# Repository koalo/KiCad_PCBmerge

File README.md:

# KiCad_PCBmerge

A Python module for merging multiple KiCad PCBs

By using this module you can merge multiple KiCad PCBs by aligning them at a common part.
For example for merging a addon board to a base board and align them at a pin header use the following steps.

1. Create a KiCad PCB for the base PCB and add a pin header where the addon board shall be connected.
2. Change the value of the pin header to a specific value, for example OUTPUT.
2. Create a second PCB for the addon board and add a pin header for example with the name INPUT, too.
3. Download the pcbmerge.py and create a Python script with the following content

        #!/usr/bin/env python

        from pcbnew import *
        import pcbmerge

        # Load the power board
        mypcb = LoadBoard("NAME_OF_THE_BASE.kicad_pcb")

        # Merge the power board with the led board
        pcbmerge.merge(pcb = mypcb,
                       base_anchor = "OUTPUT",
                       addon_anchor = "INPUT",
                       filename = "NAME_OF_THE_ADDON.kicad_pcb")

        # Combine and refill areas
        pcbmerge.combine_all_areas(mypcb)
        pcbmerge.fill_all_areas(mypcb)

        # Save output
        SaveBoard("simple.kicad_pcb", mypcb)

4. Execute the script and open the simple.kicad_pcb

# License

This is free and unencumbered software released into the public domain.

Anyone is free to copy, modify, publish, use, compile, sell, or
distribute this software, either in source code form or as a compiled
binary, for any purpose, commercial or non-commercial, and by any
means.

In jurisdictions that recognize copyright laws, the author or authors
of this software dedicate any and all copyright interest in the
software to the public domain. We make this dedication for the benefit
of the public at large and to the detriment of our heirs and
successors. We intend this dedication to be an overt act of
relinquishment in perpetuity of all present and future rights to this
software under copyright law.

THE SOFTWARE IS PROVIDED "AS IS", WITHOUT WARRANTY OF ANY KIND,
EXPRESS OR IMPLIED, INCLUDING BUT NOT LIMITED TO THE WARRANTIES OF
MERCHANTABILITY, FITNESS FOR A PARTICULAR PURPOSE AND NONINFRINGEMENT.
IN NO EVENT SHALL THE AUTHORS BE LIABLE FOR ANY CLAIM, DAMAGES OR
OTHER LIABILITY, WHETHER IN AN ACTION OF CONTRACT, TORT OR OTHERWISE,
ARISING FROM, OUT OF OR IN CONNECTION WITH THE SOFTWARE OR THE USE OR
OTHER DEALINGS IN THE SOFTWARE.

For more information, please refer to <http://unlicense.org>

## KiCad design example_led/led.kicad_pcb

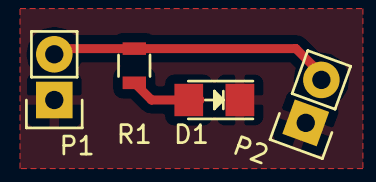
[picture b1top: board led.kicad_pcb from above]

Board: 2 copper layers, 4 parts (0 on the bottom side), 3 nets.

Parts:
D1: LED; LED_1206
P1: IN; Pin_Header_Straight_1x02
P2: OUT; Pin_Header_Straight_1x02
R1: 220R; R_0805

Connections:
Earth: D1.1, P1.1, P2.1
unnamed: D1.2, R1.2
unnamed: P1.2, P2.2, R1.1

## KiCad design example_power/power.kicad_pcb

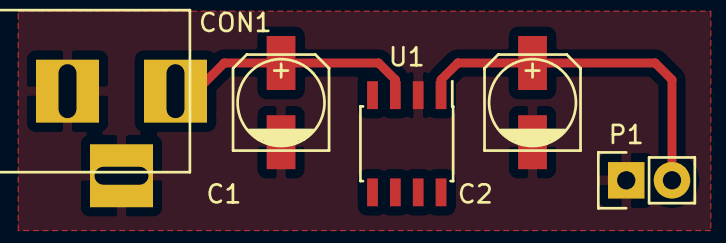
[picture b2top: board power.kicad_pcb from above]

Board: 2 copper layers, 5 parts (0 on the bottom side), 3 nets.

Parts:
C1, C2: 10 uF; c_elec_5x5.7
CON1: BARREL_JACK
P1: OUTPUT; Pin_Header_Straight_1x02
U1: LM78L05ACZ; SOIC-8_3.9x4.9mm_Pitch1.27mm

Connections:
Earth: C1.2, C2.2, CON1.2, CON1.3, P1.1, U1.2
unnamed: C1.1, CON1.1, U1.3
unnamed: C2.1, P1.2, U1.1

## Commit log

2016-10-07 Release KiCad_PCBmerge
2016-10-07 Example
2016-10-07 Refill Areas
2016-10-07 Combine areas
2016-10-07 Recursive example
2016-10-07 README enhanced
2023-04-16 Update script to the KiCad 7 API.
2023-04-16 Add missing newline at the end of file.
